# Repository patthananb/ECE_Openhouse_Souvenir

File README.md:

# KMUTNB ECE Souvenir PCB

30 × 30 mm souvenir board. TOP: ECE KMUTNB logo silkscreen. BOTTOM: CMOS 555
astable blinking 14 orange 0402 LEDs laid out as 7-segment "ECE".
KiCad 10.0.6. Sources generated by scripts in `tools/`.

## Layout

| Path | What |
|---|---|
| `tools/parts.py` | BOM single source of truth (refs, values, footprints, LCSC codes) |
| `tools/gen_sch.py` | Generates `hardware/ece_souvenir.kicad_sch` |
| `tools/check_netlist.py` | Exports netlist via kicad-cli and diffs against spec |
| `tools/logo_trace.py` | Rasterises `art/ece_logo.png` into silkscreen runs (`art/ece_logo_runs.json`) |
| `tools/gen_pcb.py` | Generates `hardware/ece_souvenir.kicad_pcb`: outline, hole, placement, logo, rules (KiCad Python) |
| `tools/route.py` | Autoroutes: KiCad DSN export → Konnect `route_specctra_dsn` (local Freerouting 2.4.1) → KiCad SES import |
| `tools/konnect_mcp.py` | Minimal stdio client for the Konnect MCP server |
| `tools/emi_check.py` | EMI routing-geometry audit: right-angle/acute bends, stubs, copper-to-edge, widths |
| `tools/cost_estimate.py` | Cost estimate: full assembly vs DIY vs bare PCB (live JLCPCB/LCSC part prices) |
| `hardware/` | KiCad project |

## Circuit

555 astable (TLC555, CMOS). Q1 (MMBT3906 PNP) is a high-side switch fed from 555 OUT through
R6 = 4.7 kΩ: it conducts while OUT is LOW (discharge phase), so the LEDs flash briefly. Each digit
has one shared current-limit resistor (advisor review 2026-10-11); LED cathodes go to GND.

| Quantity | Formula | Value |
|---|---|---|
| t_on (LEDs lit) | 0.693·R2·C1 | 83 ms |
| t_off | 0.693·(R1+R2)·C1 | 776 ms |
| f | 1/(t_on+t_off) | 1.16 Hz, duty 9.7 % |
| I per digit | (VCC − Vce_sat − Vf)/R; E: 680 Ω, orange Vf ≈ 1.85 V; C: 220 Ω, white Vf ≈ 2.6 V | E ≈ 2.0 → 4.5 mA, C ≈ 2.9 → 10.5 mA (3.3 → 5 V) |
| I per LED (avg of digit) | I_digit / n | orange ≈ 0.4 → 0.9 mA (≈ 6 → 14 mcd), white ≈ 0.7 → 2.6 mA (≈ 5 → 17 mcd) |
| Q1 load / base | Σ digits; (VCC − V_EB − V_OL)/3.3 kΩ | ≤ 19.5 mA; I_B 0.8 … 1.3 mA (forced β ≈ 9–15) |

Design notes:
- Without Q1 the TLC555 could sink the ≈13 mA directly (100 mA typ / 150 mA abs-max, TI SLFS043K);
  Q1 was added on review so the 555 only supplies base current. A PNP (not NPN) is used so the LEDs
  stay on during the short OUT-LOW phase; an NPN low-side switch would light them ≈90 % of the time.
- Shared resistors trade matching for parts count: parallel LEDs on one resistor split current by
  exp(ΔVf / nV_T) (nV_T ≈ 50 mV at ~1 mA), so a 30 mV Vf spread can mean ≈1.8× current between
  segments of one digit. Use LEDs from one reel.
- White C: only ≈ 0.65 V of headroom at 3.3 V (Vf ≈ 2.6 V + Vce_sat), so the C dims fastest as the
  supply drops; below ≈ 3.0 V (e.g. a CR2032) it will barely light. Run from ≥ 3.3 V.

## Board

- 30 × 30 mm, R1 mm corners, 2-layer FR4 1.6 mm, white mask / black silk.
- TOP: logo only, 24 × 21.3 mm on F.SilkS at (3.0, 6.0); 2.5 mm NPTH keychain hole at (27, 3).
- BOTTOM: all parts **and all copper** (single-sided routing: no top traces, no vias, so the logo side
  is bare silkscreen on white mask). LEDs stand alone at the spec positions (bottom-view x mirrored:
  `x_top = 30 − x_bv`). LED polarity is 180° (a/g/d) and 270° (f/e) instead of the spec's 0°/90°:
  identical look, but every cathode then meets at each digit's inner-left corner, which is what makes
  one-layer routing possible. Digit resistors R3/R4/R5 sit under each digit; Q1 + R6 left of U1;
  U1 at 270°; C2 centre 1.96 mm from pin 8. Pads: + / − bottom right, OUT probe beside R6.
- One-layer topology (locked pre-routes in `tools/route.py`): TH (pin 2) and GND (pin 1) run under
  the SOIC body out of its left end; VCC is a ring round the board edge from pin 4 to pin 8, which
  keeps the LED field, Q1, OUT and pin 1 on the same side of every barrier.
- Board placed on the drawing sheet at (111.1825, 56.0585) mm; grid and drill/place origins are set
  to the board's top-left corner, so coordinates still read (0,0) at top-left.
- Hand-solder safety: router keepouts forbid foreign traces between the pads of every 2-pad part;
  `tools/route.py` also reports any trace between two pads of one part (currently none).
- EMI routing rules (checked by `tools/emi_check.py`):
  - no 90° or acute corners: pre-routes are drawn at 45°, autorouted corners are mitred to 45°
    (DRC-guarded); single layer, so there are no cross-layer crossings to keep perpendicular;
  - all copper ≥ 1.0 mm from the board edge (VCC ring centreline 1.15 mm, router boundary inset 0.5 mm);
  - B.Cu GND pour in all free space (0.3 mm clearance, thermal spokes for hand soldering, islands
    removed, so no floating copper) gives every trace an adjacent return path and guards the
    high-impedance TH/DIS nodes;
  - short explicit decoupling loop C2 ↔ U1 pin 1/8 (C2 centre 1.96 mm from pin 8);
  - timing cap C1 sits at the left end of U1 between the TH and GND under-body lanes (~1 mm loop);
  - LED_PWR (switched LED current) is one straight 0.3 mm bus; VCC/GND/LED_PWR in the 0.3 mm
    `Power` class; no stubs, no vias.
- Rules (in `.kicad_pro`): track/clearance ≥ 0.20 mm, via 0.6/0.3 mm, copper–edge 0.3 mm,
  silk line ≥ 0.15 mm, text ≥ 1.0 mm. Net class `Power` (VCC, GND, LED_PWR) 0.3 mm.

## Parts (LCSC, checked 2026-10-11) — hand-soldered, nothing below 0603

All passives/LEDs use KiCad `*_0603_*_HandSolder` footprints; Q1 uses `SOT-23_Handsoldering`.

| Ref | Part | LCSC |
|---|---|---|
| U1 | TI TLC555CDR, 2–15 V CMOS 555, SOIC-8 | C6986 |
| Q1 | onsemi MMBT3906LT1G PNP, SOT-23 | C53444 |
| D1–D5, D10–D14 (E, E) | XINGLIGHT XL-1608UOC-06 orange 605 nm 0603 | C965800 |
| D6–D9 (C) | XINGLIGHT XL-1608UWC-04 white 0603, Vf 2.7 V @ 20 mA | C965808 |
| C1 | Yageo CC0603KRX7R7BB105, 1 µF 16 V X7R | C106248 |
| C2 / C3 | 100 nF 50 V X7R / 10 nF 50 V X7R 0603 | C14663 / C57112 |
| R1 / R2 | 1 MΩ / 120 kΩ 1 % 0603 | C22935 / C25808 |
| R3, R5 / R4 | 680 Ω (orange E digits) / 220 Ω (white C digit) 1 % 0603 | C23228 / C22962 |
| R6 | 3.3 kΩ 1 % 0603 (Q1 base) | C22978 |

## Cost estimate (2026-10-12, USD incl. shipping to Thailand)

`python3 tools/cost_estimate.py 10 50 100 300 500`. Part prices are live (JLCPCB parts API for
assembly, LCSC API for retail MOQ). Assumptions in the script header: JLCPCB Economic PCBA (setup
$8, stencil $1.50, $0.0017/joint, $3 per extended part × 5), bare-PCB price model (5 pcs = $4.00 on
the live quote; larger quantities modelled), shipping JLCPCB $12–32, LCSC $8–25. Ranges = low–high.

| Qty | 1. Full assembly | 2. DIY (PCB + LCSC parts) | 3. Bare PCB only |
|---|---|---|---|
| 10 | $47–71 ($4.67–7.07/pc) | $35–76 ($3.46–7.56/pc) | $17–41 ($1.70–4.10/pc) |
| 50 | $67–93 ($1.34–1.86/pc) | $52–95 ($1.04–1.90/pc) | $20–46 ($0.40–0.92/pc) |
| 100 | $91–120 ($0.91–1.20/pc) | $73–119 ($0.73–1.19/pc) | $23–52 ($0.23–0.52/pc) |
| 300 | $181–219 ($0.60–0.73/pc) | $147–202 ($0.49–0.67/pc) | $34–72 ($0.11–0.24/pc) |
| 500 | $245–288 ($0.49–0.58/pc) | $196–256 ($0.39–0.51/pc) | $44–87 ($0.09–0.17/pc) |

DIY excludes soldering labour (25 parts / 57 joints per board) and consumables. Confirm the PCB and
PCBA lines on cart.jlcpcb.com before ordering; Thai import VAT may apply.

## Testing

Regenerate schematic, normalise to KiCad 10 format, run ERC and netlist check:

```bash
python3 tools/gen_sch.py && \
/Applications/KiCad/KiCad.app/Contents/MacOS/kicad-cli sch upgrade hardware/ece_souvenir.kicad_sch && \
/Applications/KiCad/KiCad.app/Contents/MacOS/kicad-cli sch erc --severity-all --exit-code-violations -o hardware/erc.rpt hardware/ece_souvenir.kicad_sch && \
python3 tools/check_netlist.py
```

Expected output (macOS 27, KiCad 10.0.6, Python 3.10):

```
wrote hardware/ece_souvenir.kicad_sch
Successfully saved schematic file using the latest format
Found 0 violations
Saved ERC Report to hardware/erc.rpt
10 named nets + 1 unnamed net: OK
```

`hardware/erc.rpt` contains `** ERC messages: 0  Errors 0  Warnings 0`; all commands exit 0.

Regenerate the board and run DRC with schematic parity (KiCad's bundled Python provides `pcbnew`):

```bash
python3 tools/logo_trace.py && \
/Applications/KiCad/KiCad.app/Contents/Frameworks/Python.framework/Versions/3.9/bin/python3 tools/gen_pcb.py && \
/Applications/KiCad/KiCad.app/Contents/MacOS/kicad-cli pcb drc --schematic-parity --severity-all -o hardware/drc.rpt hardware/ece_souvenir.kicad_pcb
```

Expected output, placement phase (unrouted; KiCad prints some wx debug lines on stderr, which you can ignore):

```
7877 rects, 24.0 x 21.29 mm at (3.0, 6.0), 14.1 um/px -> art/ece_logo_runs.json
wrote hardware/ece_souvenir.kicad_pcb; logo polygons: 48
Found 0 violations
Found 49 unconnected items
Found 0 schematic parity issues
Saved DRC Report to hardware/drc.rpt
```

The 49 unconnected items are expected until the routing phase.

### Routing (single-sided)

Requires Konnect 0.13.0 (KiCad PCM plugin, `~/Documents/KiCad/10.0/3rdparty/plugins/com_github_mixelpixx_konnect`),
Freerouting 2.4.1 jar + Temurin JRE 25 in `~/.local/share/freerouting/`, KiCad GUI closed. Konnect's own
Specctra exporter only accepts front-side parts / rect pads / straight outlines, so KiCad's native DSN
exporter and SES importer do the file conversion and Konnect's `route_specctra_dsn` drives Freerouting.
DSN tweaks: boundary inset 0.1 mm (0.3 mm edge rule), F.Cu inactive and vias off (one layer), and
between-pad keepouts. Note: Freerouting 2.4.1 silently ignores the whole netlist if a `keepout`
precedes `autoroute_settings` in `(structure ...)`.

```bash
/Applications/KiCad/KiCad.app/Contents/Frameworks/Python.framework/Versions/3.9/bin/python3 tools/route.py 60 && \
/Applications/KiCad/KiCad.app/Contents/MacOS/kicad-cli pcb drc --schematic-parity --severity-all -o hardware/drc.rpt hardware/ece_souvenir.kicad_pcb
```

Expected output for the committed board (Freerouting is heuristic: segment counts/length can differ
between runs; what must hold is 0 F.Cu, 0 vias, 0 crossings, DRC all zero):

```
route_specctra_dsn: {'isError': False, 'result': {... 'final_state': 'COMPLETED', ... 'success': True}}
widened 8 neck-down segments to net-class width
mitred 3/3 corners >= 90 deg to 45 deg (0 reverted by DRC)
GND pour on B.Cu: 422.7 mm^2 filled
imported hardware/routing/ece_souvenir-<stamp>.ses: 129 B.Cu segs (297.8 mm), 0 F.Cu segs (0.0 mm), 0 vias
between-pad crossings: 0
Found 0 violations
Found 0 unconnected items
Found 0 schematic parity issues
Saved DRC Report to hardware/drc.rpt
```

### EMI geometry audit

```bash
/Applications/KiCad/KiCad.app/Contents/Frameworks/Python.framework/Versions/3.9/bin/python3 tools/emi_check.py
```

Expected output (exit 0):

```
bends: 0 right-angle, 0 acute (>90 deg turn); T-junctions: 10; vias: 0
stubs: 0
copper-to-edge: min 1.00 mm (/TH); 0 segments closer than 1.0 mm (nets: [])
nets: width mm / length mm
  /A_C         [0.2]   20.6
  /A_E1        [0.2]   26.5
  /A_E2        [0.2]   23.5
  /CV          [0.2]    2.2
  /DIS         [0.2]    4.0
  /LED_PWR     [0.3]   16.9
  /OUT         [0.2]    5.3
  /TH          [0.2]   18.3
  GND          [0.3]   72.0
  Net-(Q1-B)   [0.2]    6.9
  VCC          [0.3]  101.6
EMI geometry: PASS
```

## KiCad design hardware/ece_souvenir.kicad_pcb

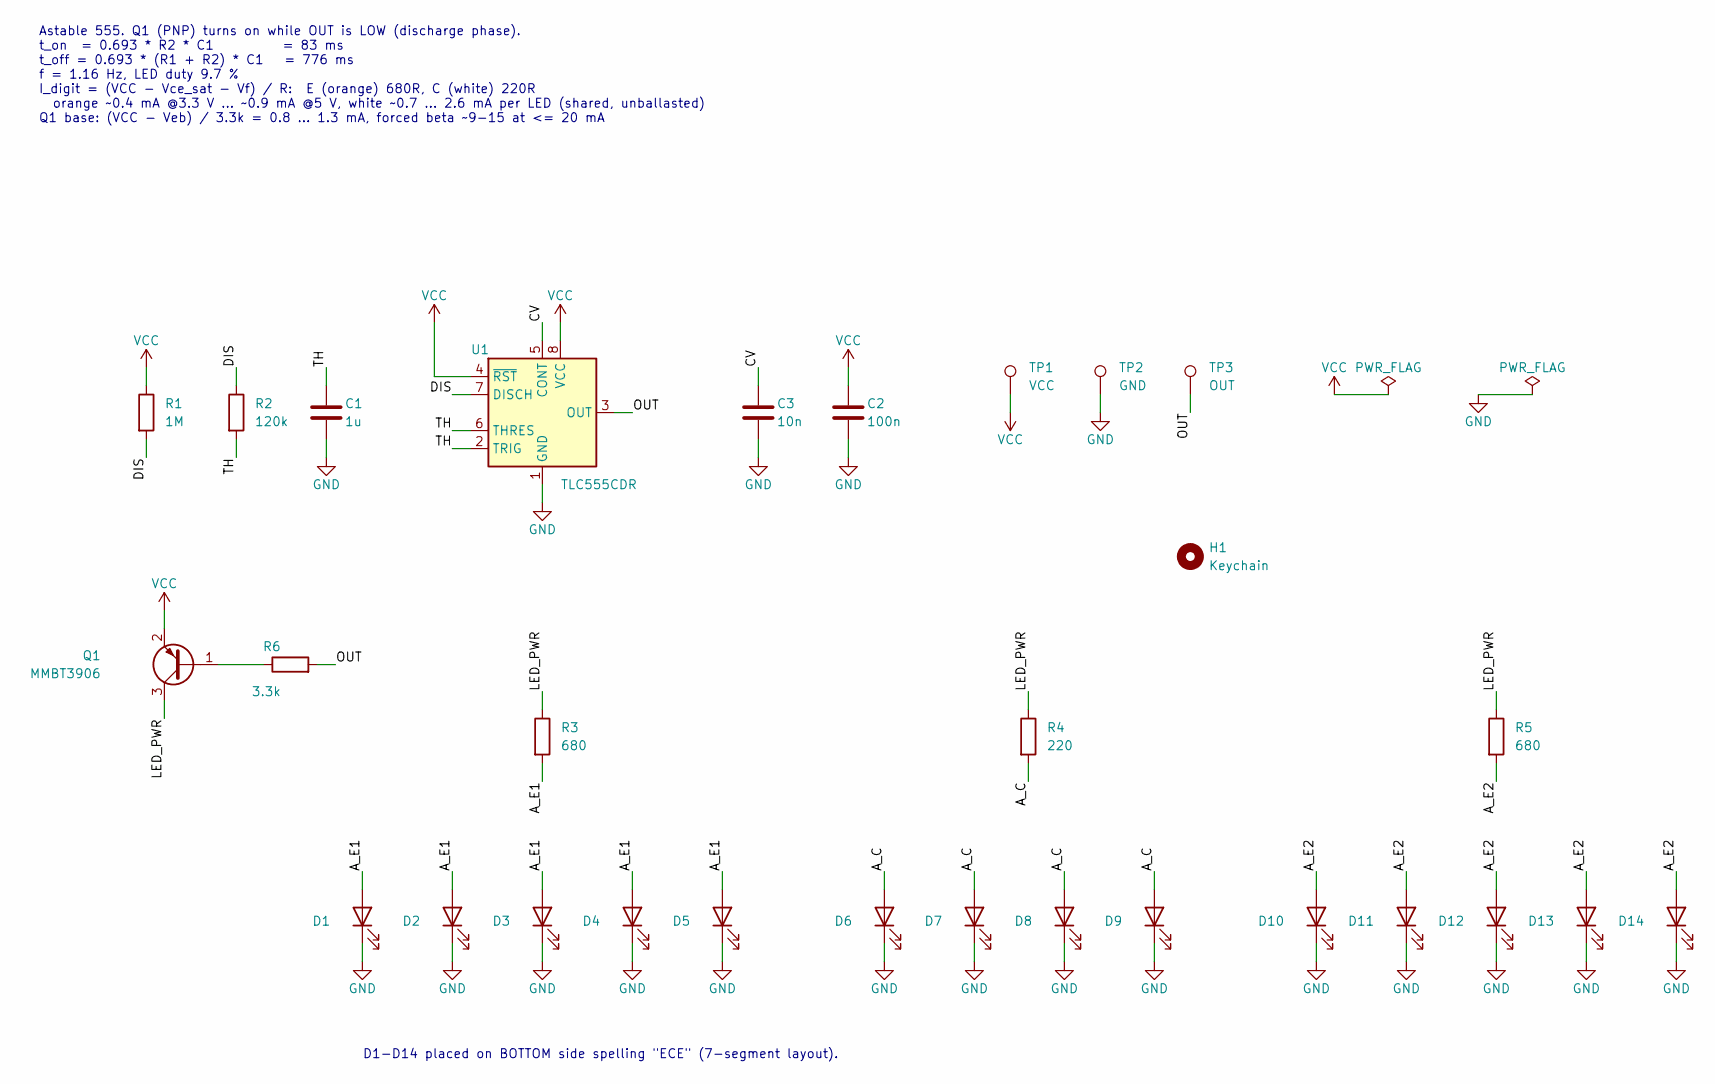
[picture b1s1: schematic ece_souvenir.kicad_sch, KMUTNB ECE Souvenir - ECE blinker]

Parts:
C1: 1u; C_0603_1608Metric_Pad1.08x0.95mm_HandSolder; MPN CC0603KRX7R7BB105; LCSC C106248
C2: 100n; C_0603_1608Metric_Pad1.08x0.95mm_HandSolder; MPN CC0603KRX7R9BB104; LCSC C14663
C3: 10n; C_0603_1608Metric_Pad1.08x0.95mm_HandSolder; MPN 0603B103K500NT; LCSC C57112
D1, D2, D3, D4, D5, D10, D11, D12, D13, D14: Orange; LED_0603_1608Metric_Pad1.05x0.95mm_HandSolder; MPN XL-1608UOC-06; LCSC C965800
D6, D7, D8, D9: White; LED_0603_1608Metric_Pad1.05x0.95mm_HandSolder; MPN XL-1608UWC-04; LCSC C965808
H1: Keychain; MountingHole_2.5mm
Q1: MMBT3906; SOT-23_Handsoldering; MPN MMBT3906LT1G; LCSC C53444
R1: 1M; R_0603_1608Metric_Pad0.98x0.95mm_HandSolder; MPN 0603WAF1004T5E; LCSC C22935
R2: 120k; R_0603_1608Metric_Pad0.98x0.95mm_HandSolder; MPN 0603WAF1203T5E; LCSC C25808
R3, R5: 680; R_0603_1608Metric_Pad0.98x0.95mm_HandSolder; MPN 0603WAF6800T5E; LCSC C23228
R4: 220; R_0603_1608Metric_Pad0.98x0.95mm_HandSolder; MPN 0603WAF2200T5E; LCSC C22962
R6: 3.3k; R_0603_1608Metric_Pad0.98x0.95mm_HandSolder; MPN 0603WAF3301T5E; LCSC C22978
TP1: VCC; TestPoint_Pad_D2.0mm
TP2: GND; TestPoint_Pad_D2.0mm
TP3: OUT; TestPoint_Pad_D1.5mm
U1: TLC555CDR; SOIC-8_3.9x4.9mm_P1.27mm; MPN TLC555CDR; LCSC C6986

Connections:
/A_C: D6.2 (A), D7.2 (A), D8.2 (A), D9.2 (A), R4.2
/A_E1: D1.2 (A), D2.2 (A), D3.2 (A), D4.2 (A), D5.2 (A), R3.2
/A_E2: D10.2 (A), D11.2 (A), D12.2 (A), D13.2 (A), D14.2 (A), R5.2
/CV: C3.1, U1.5 (CONT)
/DIS: R1.2, R2.1, U1.7 (DISCH)
/LED_PWR: Q1.3 (C), R3.1, R4.1, R5.1
/OUT: R6.2, TP3.1, U1.3 (OUT)
/TH: C1.1, R2.2, U1.2 (TRIG), U1.6 (THRES)
GND: C1.2, C2.2, C3.2, D1.1 (K), D2.1 (K), D3.1 (K), D4.1 (K), D5.1 (K), D6.1 (K), D7.1 (K), D8.1 (K), D9.1 (K), D10.1 (K), D11.1 (K), D12.1 (K), D13.1 (K), D14.1 (K), TP2.1, U1.1 (GND)
unnamed: Q1.1 (B), R6.1
VCC: C2.1, Q1.2 (E), R1.1, TP1.1, U1.4 (~RST), U1.8 (VCC)

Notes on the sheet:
Astable 555. Q1 (PNP) turns on while OUT is LOW (discharge phase). t_on = 0.693 * R2 * C1 = 83 ms t_off = 0.693 * (R1 + R2) * C1 = 776 ms f = 1.16 Hz, LED duty 9.7 % I_digit = (VCC - Vce_sat - Vf) / R: E (orange) 680R, C (white) 220R orange ~0.4 mA @3.3 V ... ~0.9 mA @5 V, white ~0.7 ... 2.6 mA per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
D1-D14 placed on BOTTOM side spelling "ECE" (7-segment layout).

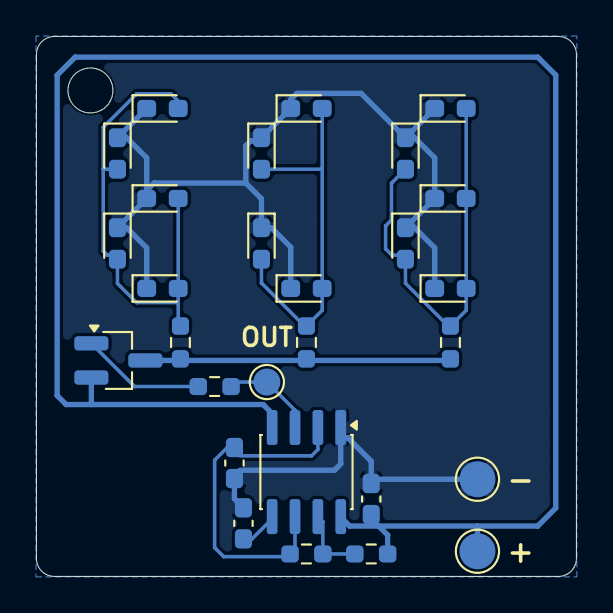
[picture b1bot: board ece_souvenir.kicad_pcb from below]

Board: 2 copper layers, 30.0 x 30.0 mm, 29 parts (28 on the bottom side), 11 nets.
